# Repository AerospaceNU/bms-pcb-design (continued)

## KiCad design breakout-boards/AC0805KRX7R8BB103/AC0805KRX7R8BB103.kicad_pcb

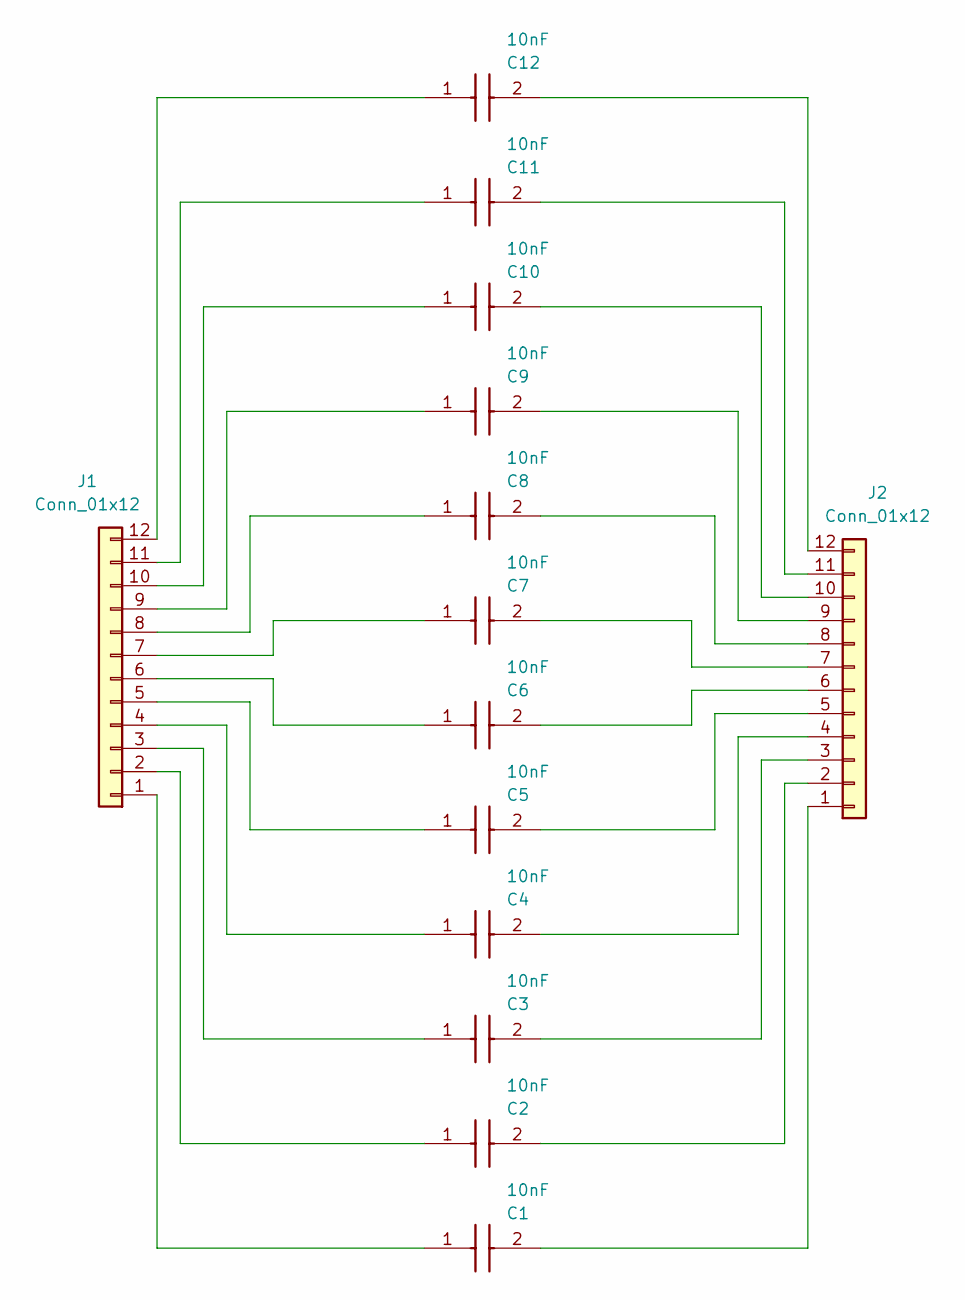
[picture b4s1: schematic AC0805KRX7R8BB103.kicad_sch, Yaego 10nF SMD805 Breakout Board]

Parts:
C1, C2, C3, C4, C5, C6, C7, C8, C9, C10, C11, C12: 10nF; CAPC2012X95N; Mouser Part Number 603-AC805KRX7R8BB103
J1, J2: Conn_01x12; PinSocket_1x12_P2.54mm_Vertical

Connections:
unnamed: C1.1, J1.1
unnamed: C2.1, J1.2
unnamed: C3.1, J1.3
unnamed: C4.1, J1.4
unnamed: C5.1, J1.5
unnamed: C6.1, J1.6
unnamed: C7.1, J1.7
unnamed: C8.1, J1.8
unnamed: C9.1, J1.9
unnamed: C10.1, J1.10
unnamed: C11.1, J1.11
unnamed: C12.1, J1.12
unnamed: C1.2, J2.1
unnamed: C2.2, J2.2
unnamed: C3.2, J2.3
unnamed: C4.2, J2.4
unnamed: C5.2, J2.5
unnamed: C6.2, J2.6
unnamed: C7.2, J2.7
unnamed: C8.2, J2.8
unnamed: C9.2, J2.9
unnamed: C10.2, J2.10
unnamed: C11.2, J2.11
unnamed: C12.2, J2.12

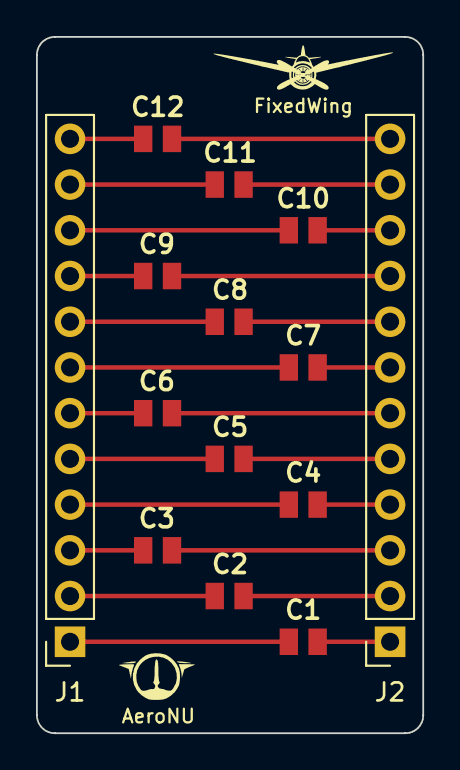
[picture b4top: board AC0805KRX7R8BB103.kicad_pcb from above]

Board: 2 copper layers, 21.5 x 38.7 mm, 16 parts (0 on the bottom side), 24 nets.

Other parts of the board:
AeroNU: LOGO; AeroNU - Logo (Smol)
FixedWing: LOGO; FixedWing - Logo (Smol)

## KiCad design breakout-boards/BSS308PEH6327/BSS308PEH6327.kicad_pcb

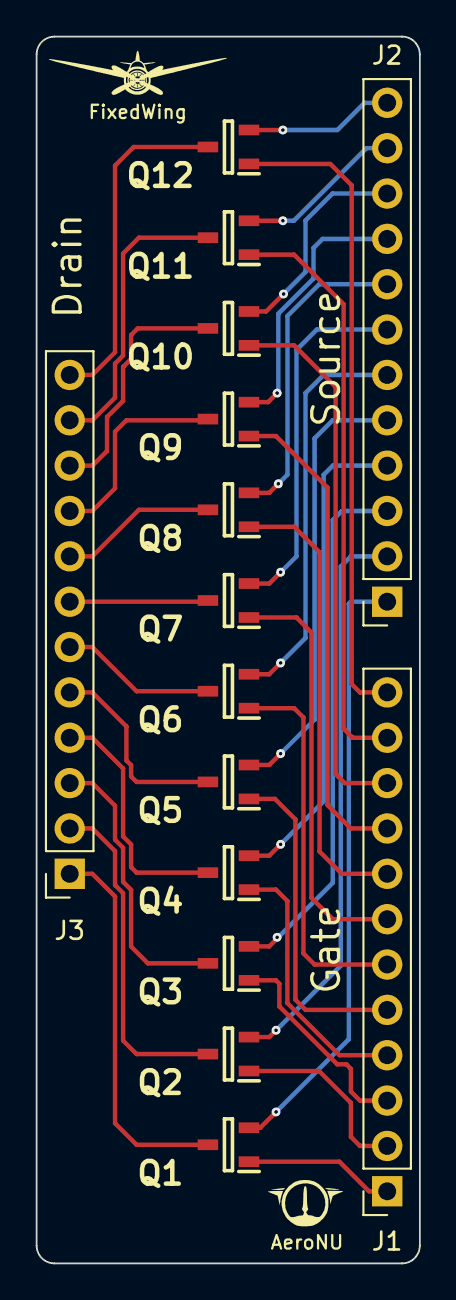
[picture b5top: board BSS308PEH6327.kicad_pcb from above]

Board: 2 copper layers, 21.5 x 68.7 mm, 17 parts (0 on the bottom side), 4 nets.

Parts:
AeroNU: LOGO; AeroNU - Logo (Smol)
FixedWing: LOGO; FixedWing - Logo (Smol)
J1, J2, J3: Conn_01x12; PinSocket_1x12_P2.54mm_Vertical
Q1, Q2, Q3, Q4, Q5, Q6, Q7, Q8, Q9, Q10, Q11, Q12: BSS308PE_H6327; SOT95P260X110-3N

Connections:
unnamed: J2.10, Q10.2 (S)
unnamed: J2.9, Q9.2 (S)
unnamed: J2.8, Q8.2 (S)
unnamed: J2.1, Q1.2 (S)

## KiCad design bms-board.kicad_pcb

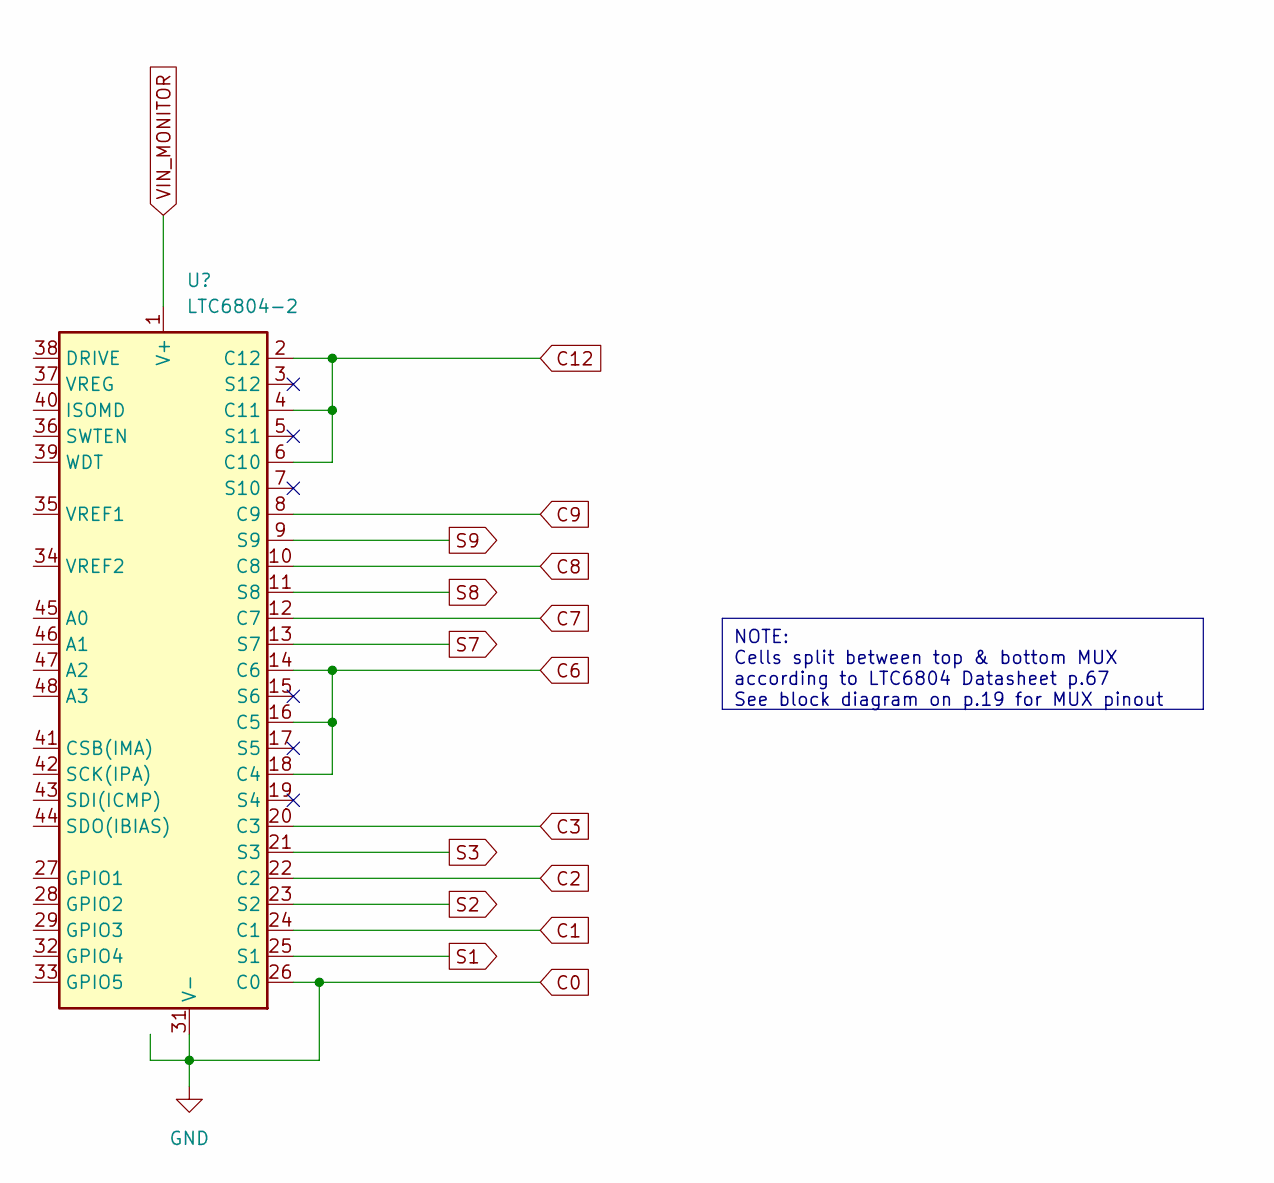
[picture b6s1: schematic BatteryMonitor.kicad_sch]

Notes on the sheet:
NOTE: Cells split between top & bottom MUX according to LTC6804 Datasheet p.67 See block diagram on p.19 for MUX pinout

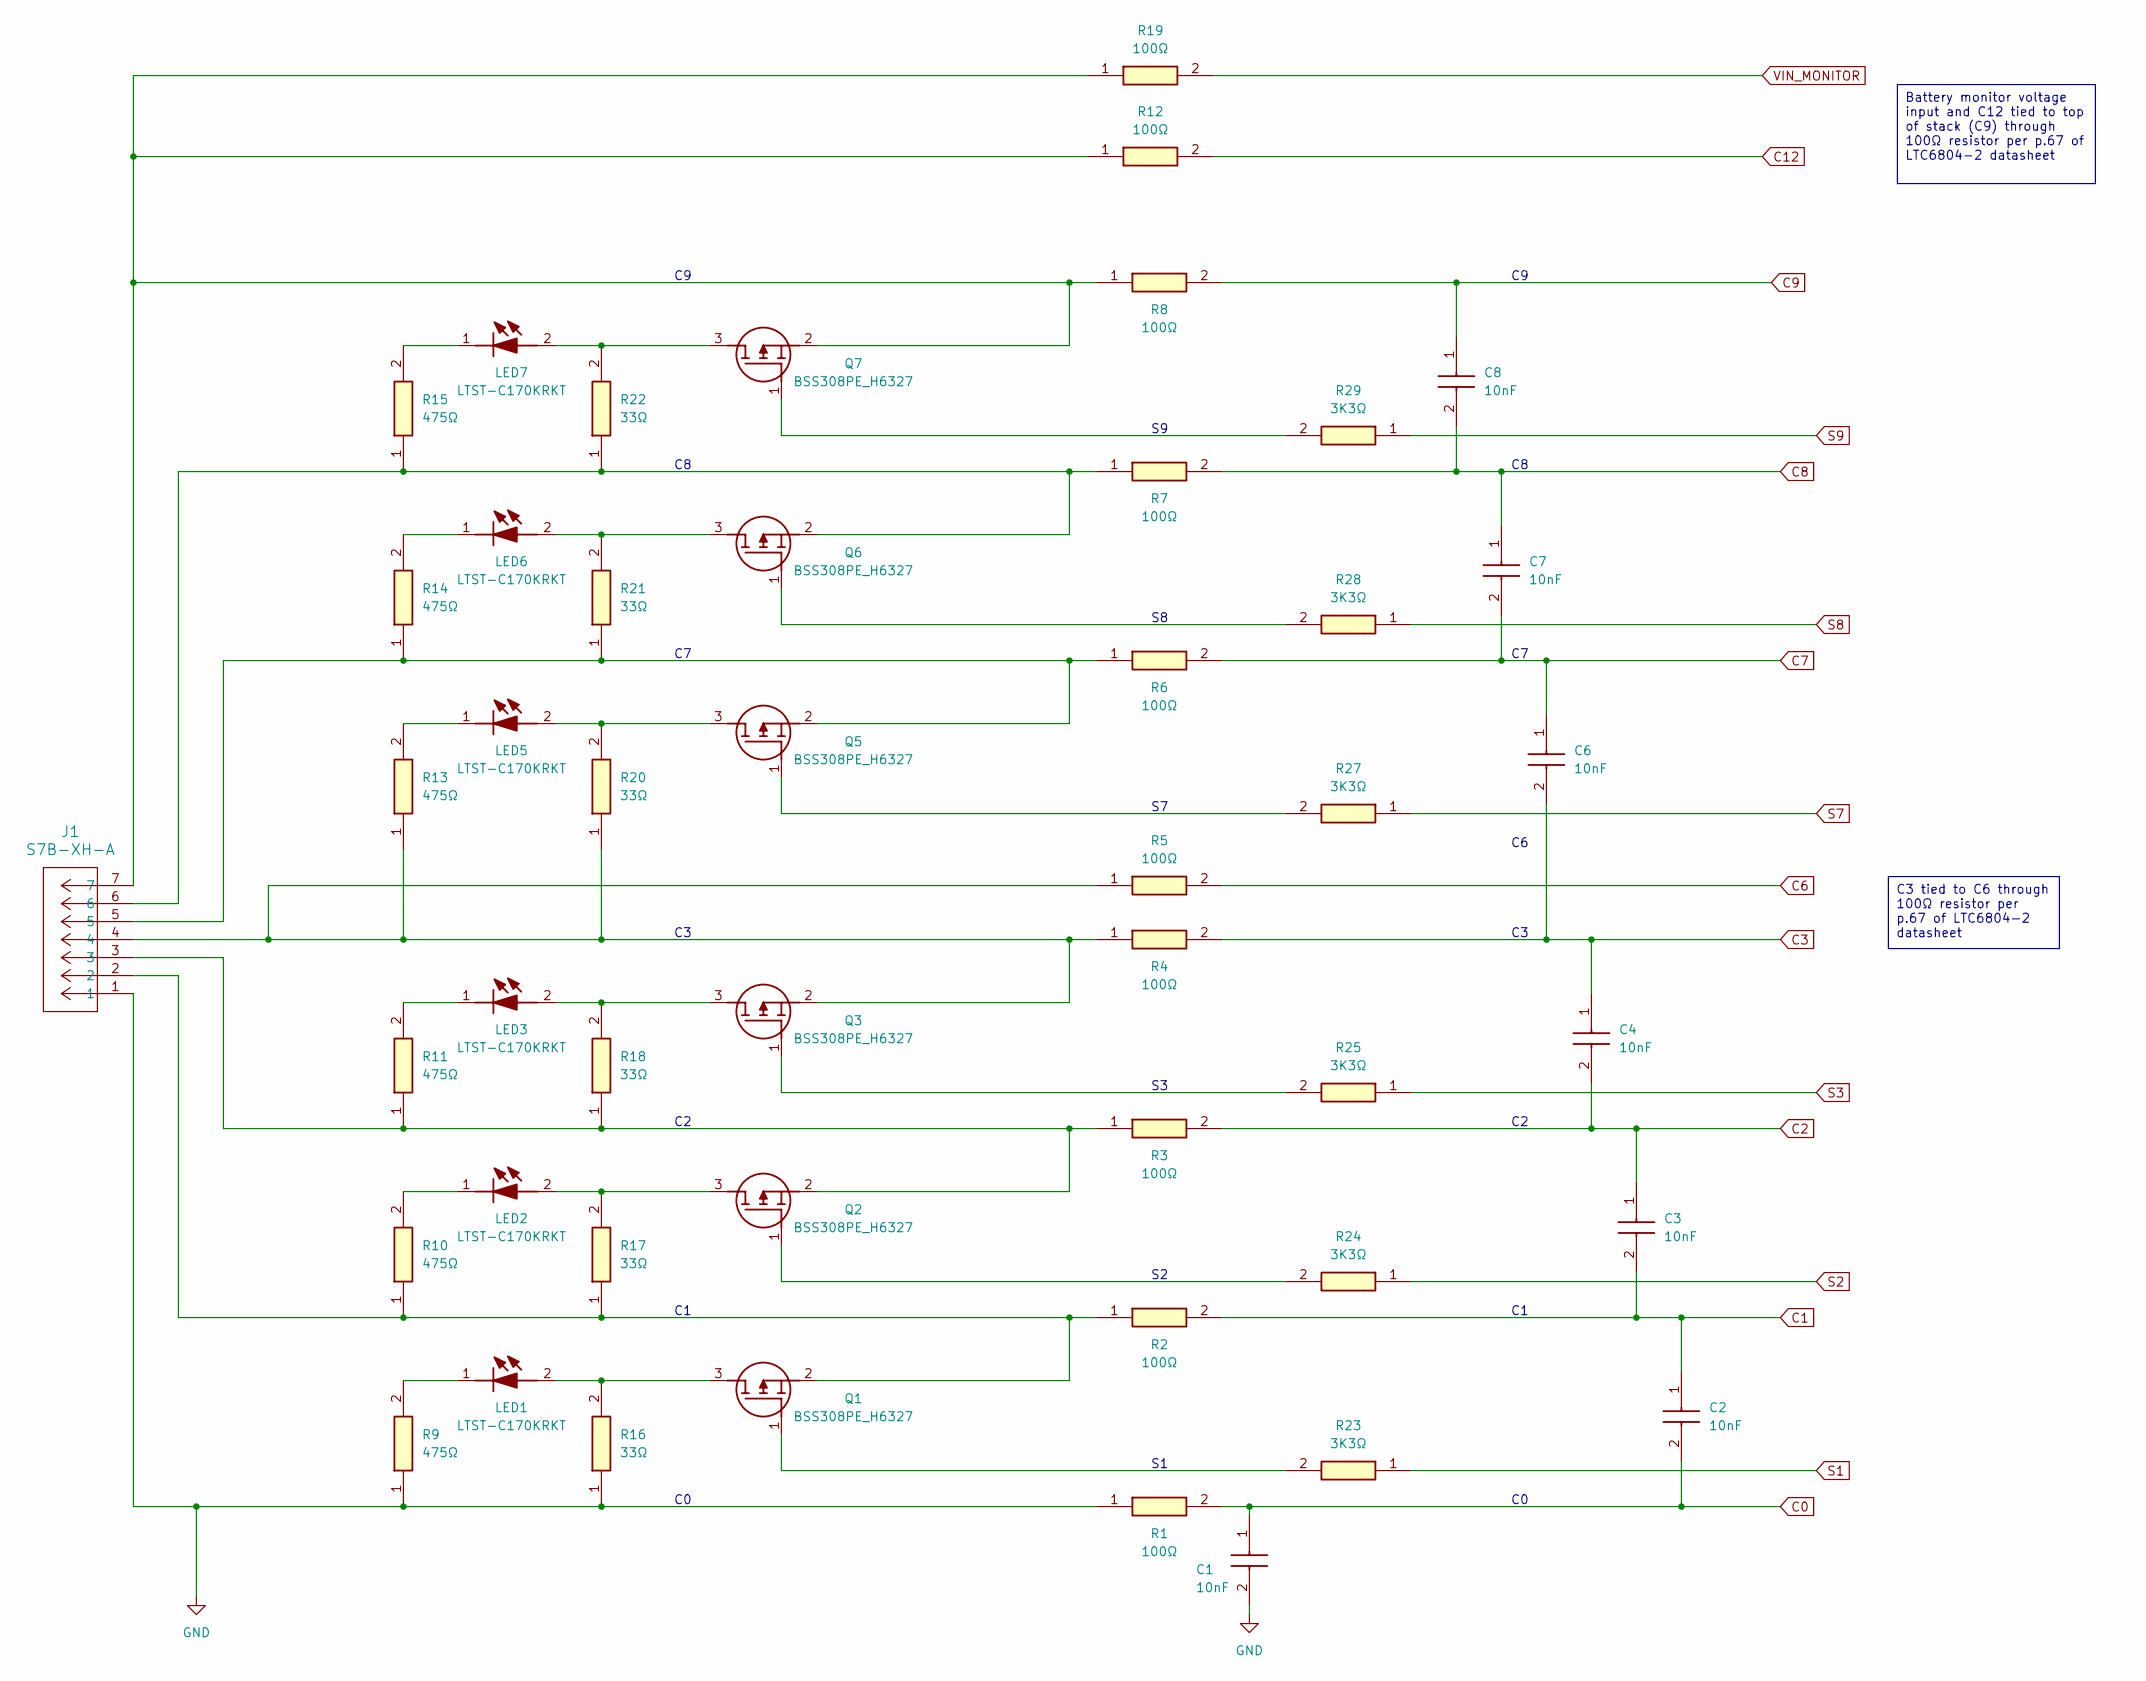
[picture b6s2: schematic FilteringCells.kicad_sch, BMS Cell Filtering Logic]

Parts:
C1, C2, C3, C4, C6, C7, C8: 10nF; CAPC2012X95N; Mouser Part Number 603-AC805KRX7R8BB103
J1: S7B-XH-A; CONN_S7B-XH-A_JST
LED1, LED2, LED3, LED5, LED6, LED7: LTST-C170KRKT; LEDC2012X120N; Mouser Part Number 859-LTST-C170KRKT
Q1, Q2, Q3, Q5, Q6, Q7: BSS308PE_H6327; SOT95P260X110-3N; Mouser Part Number 726-BSS308PEH6327
R1, R2, R3, R4, R5, R6, R7, R8, R12, R19: 100Ω; RESC2012X50N; Mouser Part Number 71-CRCW0805-100-E3
R9, R10, R11, R13, R14, R15: 475Ω; RESC2012X50N; Mouser Part Number 71-CRCW0805-475-E3
R16, R17, R18, R20, R21, R22: 33Ω; RESC6332X70N; Manufacturer_Part_Number CRCW251233R0FKEG
R23, R24, R25, R27, R28, R29: 3K3Ω; RESC2012X50N; Mouser Part Number 71-CRCW08053K30JNEA

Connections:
C0: C1.1, C1.2, C2.2, J1.1, R1.1, R1.2, R9.1, R16.1; also elsewhere on the board
C1: C2.1, C3.2, R2.2; also elsewhere on the board
C2: C3.1, C4.2, R3.2; also elsewhere on the board
C3: C4.1, C6.2, R4.2; also elsewhere on the board
C6: R5.2; also elsewhere on the board
C7: C6.1, C7.2, R6.2; also elsewhere on the board
C8: C7.1, C8.2, R7.2; also elsewhere on the board
C9: C8.1, R8.2; also elsewhere on the board
C12: R12.2; also elsewhere on the board
unnamed: LED1.2 (A), Q1.3 (D), R16.2
unnamed: LED1.1 (K), R9.2
unnamed: LED2.2 (A), Q2.3 (D), R17.2
unnamed: LED2.1 (K), R10.2
unnamed: LED3.2 (A), Q3.3 (D), R18.2
unnamed: LED3.1 (K), R11.2
unnamed: LED5.2 (A), Q5.3 (D), R20.2
unnamed: LED5.1 (K), R13.2
unnamed: LED6.2 (A), Q6.3 (D), R21.2
unnamed: LED6.1 (K), R14.2
unnamed: LED7.2 (A), Q7.3 (D), R22.2
unnamed: LED7.1 (K), R15.2
unnamed: Q1.1 (G), R23.2
unnamed: J1.2, Q1.2 (S), R2.1, R10.1, R17.1
unnamed: Q2.1 (G), R24.2
unnamed: J1.3, Q2.2 (S), R3.1, R11.1, R18.1
unnamed: Q3.1 (G), R25.2
unnamed: J1.4, Q3.2 (S), R4.1, R5.1, R13.1, R20.1
unnamed: Q5.1 (G), R27.2
unnamed: J1.5, Q5.2 (S), R6.1, R14.1, R21.1
unnamed: Q6.1 (G), R28.2
unnamed: J1.6, Q6.2 (S), R7.1, R15.1, R22.1
unnamed: Q7.1 (G), R29.2
unnamed: J1.7, Q7.2 (S), R8.1, R12.1, R19.1
S1: R23.1; also elsewhere on the board
S2: R24.1; also elsewhere on the board
S3: R25.1; also elsewhere on the board
S7: R27.1; also elsewhere on the board
S8: R28.1; also elsewhere on the board
S9: R29.1; also elsewhere on the board
VIN_MONITOR: R19.2; also elsewhere on the board

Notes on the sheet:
C3 tied to C6 through 100Ω resistor per p.67 of LTC6804-2 datasheet
Battery monitor voltage input and C12 tied to top of stack (C9) through 100Ω resistor per p.67 of LTC6804-2 datasheet

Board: 2 copper layers, 49 parts (0 on the bottom side), 40 nets, no tracks yet.

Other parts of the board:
U1: LTC6804-2; SSOP-48_5.3x12.8mm_P0.5mm

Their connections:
C0: U1.26 (C0), U1.30 (V-), U1.31 (V-); also elsewhere on the board
C1: U1.24 (C1); also elsewhere on the board
C2: U1.22 (C2); also elsewhere on the board
C3: U1.20 (C3); also elsewhere on the board
C6: U1.14 (C6), U1.16 (C5), U1.18 (C4); also elsewhere on the board
C7: U1.12 (C7); also elsewhere on the board
C8: U1.10 (C8); also elsewhere on the board
C9: U1.8 (C9); also elsewhere on the board
C12: U1.2 (C12), U1.4 (C11), U1.6 (C10); also elsewhere on the board
S1: U1.25 (S1); also elsewhere on the board
S2: U1.23 (S2); also elsewhere on the board
S3: U1.21 (S3); also elsewhere on the board
S7: U1.13 (S7); also elsewhere on the board
S8: U1.11 (S8); also elsewhere on the board
S9: U1.9 (S9); also elsewhere on the board
VIN_MONITOR: U1.1 (V+); also elsewhere on the board

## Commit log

2024-02-13 feat: initial commit
2024-02-15 feat: add 6804-2 kicad symbol
2024-02-15 feat: add 6804-2 kicad symbol (#3)
2024-02-16 TEMPLATE: add pull request description template
2024-02-16 feat: add automated git flow setup script
2024-02-16 update feature/add-cells branch to latest develop edition (#4)
    * feat: add 6804-2 kicad symbol
    * TEMPLATE: add pull request description template
    * feat: add automated git flow setup script
2024-02-16 update feature/our-symbol-library branch to latest develop edition (#5)
    * TEMPLATE: add pull request description template
    * feat: add automated git flow setup script
2024-02-20 feat: a maybe working fixed wing schematic symbol library
2024-02-21 feat: add line to checkout dev branch when running setup script
2024-02-21 feat: fix FixedWing symbol library to include LTC6804-2
2024-02-21 refactor: verifying symbol library works, remove individual ltc6804-2 symbol
2024-02-21 feat: adding needed files
2024-02-21 feat: edit conflict in setup script
2024-02-21 Merging new develop into new feature (#6)
    * feat: add 6804-2 kicad symbol
    * TEMPLATE: add pull request description template
    * feat: add automated git flow setup script
    * update feature/our-symbol-library branch to latest develop edition (#5)
    * TEMPLATE: add pull request description template
    * feat: add automated git flow setup script
2024-02-22 fix: changed symbol for easier schematic design and orginization by pin logic
2024-02-23 docs: Update pull_request_template.md
2024-02-23 Release/0.1 (#8)
    * feat: add 6804-2 kicad symbol
    * feat: add 6804-2 kicad symbol (#3)
    * TEMPLATE: add pull request description template
    * feat: add automated git flow setup script
    * update feature/add-cells branch to latest develop edition (#4)
    * feat: add 6804-2 kicad symbol
2024-03-07 feat: started adding cell nets
2024-03-19 feat: still some more LTC6804-2 symbol edits
2024-03-21 feat: add schematic hierarchy
2024-03-21 feat: add JST-XH 7pin symbol
2024-03-28 feat: add filtering components in library
2024-03-28 feat: add more symbols, some traces, sheet template
2024-03-30 feat: add filtering circuit
2024-03-30 feat: resolved splitting cells across monitor
2024-04-02 feat: add footprints
2024-04-02 feat: update PCB schematic
2024-04-02 feat: restructure project, move libraries to parent folder
2024-04-02 feat: restructure project, move libraries to parent folder (#13)
2024-04-03 refactor: move sheet template to libraries folder
2024-04-04 fix: add relative path to AeroNU sheet template
2024-04-04 refactor: previous commit but with changes this time :)
2024-04-04 feat: add breakout board templates for filtering circuit resistors
2024-04-04 feat: add breakout boards projects for remaining components
2024-04-05 refactor: remove subdirectory backups
2024-04-05 refactor: remove backups
2024-04-05 feat: create schematic for 10nf breakout board
2024-04-05 feat: add TestPoint footprint library
2024-04-20 feat: update bms references
2024-04-20 feat: Update FixedWing lib
2024-04-20 feat: add capacitor breakout board
2024-04-20 feat: add 100ohm resistor breakout board
2024-04-20 feat: add 3.3k ohm resistor breakout board
2024-04-20 feat: add 475ohm resistor breakout board
2024-04-20 feat: add 33ohm resistor breakout board
2024-04-20 feat: add red LED breakout board
2024-04-21 feat: create footprint for capacitor breakout board
2024-04-21 feat: create footprints for resistor breakout boards
2024-04-21 feat: create footprint for LED breakout board
2024-04-21 feat: add AeroNU and FixedWing silk screen logos
2024-04-23 feat: update MOSFET pcb and schem
2024-04-23 feat: add MOSFET PCB panel
2024-04-24 feat: change fixed wing logo and component positioning
2024-04-24 feat: create capacitor board panel
2024-04-24 fix: change board alignement
2024-04-24 feat: add panel and gerber files for 3.3k ohm breakout board
2024-04-25 feat: finalize 100ohm board design
2024-04-25 feat: finalize 3.3k ohm board design
2024-04-25 feat: finalize 470ohm board design
2024-04-25 feat: finalize 33ohm board design
2024-04-25 feat: finalize LED board design
2024-05-01 feat: add fillets to all boards
2024-06-28 Feature: add cells, create breakout boards, restructure project files (#14)
    * feat: started adding cell nets
    * feat: still some more LTC6804-2 symbol edits
    * feat: add schematic hierarchy
    * feat: add JST-XH 7pin symbol
    * feat: add filtering components in library
    * feat: add more symbols, some traces, sheet template
2024-07-13 hierarchical label conversion and readability changes
2024-07-14 feat: added minimal MCU schematic, 3D component model folder
2024-07-16 feat:continuing work on integrating RP2040 MCU
2024-07-16 feat: Added 3D models for connector and Flash ROM
2024-07-16 Added 3D Models in Cell Filtering and Balancing Sch.
2024-07-16 feat. Added most 3D models for footprints
2024-07-20 feat: continuing work on MCU circuit
2024-07-21 feat: finished preliminary RP2040 schematic design
2024-07-27 Feature: Add RP2040 MCU, folder for 3D models of components, continuing edits on other schematics (#15)
    * hierarchical label conversion and readability changes
    * feat: added minimal MCU schematic, 3D component model folder
    * feat:continuing work on integrating RP2040 MCU
    * feat: Added 3D models for connector and Flash ROM
    * Added 3D Models in Cell Filtering and Balancing Sch.
    * feat. Added most 3D models for footprints
2024-08-09 feat: initial 5V-reg-and-edits branch commit
2024-08-10 feat: small to-do list edits
2024-08-11 feat: put filtering and balancing circuits into hierarchical format
2024-08-11 feat: forgot to commit smol change
2024-08-12 feat: Added SiC461 Schematic, Footprint, and 3D Model
2024-08-13 feat: Added all components listed in the spreadsheet, until Inductor L1
2024-08-14 feat: forgor the description
2024-08-14 feat: Added all symbols and 3D models. Also began working on Regulator Schematic.
2024-08-14 feat: Added more connections to the 5V Regulator schematic.
2024-08-16 feat: Added VFB connection in 5V Regulator Schematic
2024-09-11 feat: Added 220uf cap & modified 5V Reg Circuit
2024-09-11 feat: Added more to 5V Regulator Schematic
2024-09-11 feat: Changed all resistor symbols to be the standard KiCAD symbol, started improving schematic.
2024-09-11 feat: Forgot to save changes to schematic.
2024-09-11 feat: Just about completed 5V Regulator Schematic.
2024-09-12 feat: cosmetic changes to 5V reg schematic
2024-09-12 feat: Added comment boxes and fixed 5V Regulator Schematic.
2024-09-13 feat: just moved around and edited notes on the 5V reg schematic
2024-09-17 feat: re-ordered page numbers
2024-09-19 feat: Added snubber circuit to 5V Regulator schematic
2024-09-20 feat: Added 0OHM jumper between ULTRASONIC and VDD, added LED indicator for PGOOD
2024-09-20 feat: added buncha shit, refer to tasks 4 and 8
2024-09-20 feat: finished 5V reg circuit lgtm!
2024-09-22 Feature: Added schematic and symbols for 5V switching regulator (#16)
    * feat: initial 5V-reg-and-edits branch commit
    * feat: small to-do list edits
    * feat: put filtering and balancing circuits into hierarchical format
    * feat: forgot to commit smol change
    * feat: Added SiC461 Schematic, Footprint, and 3D Model
    * feat: Added all components listed in the spreadsheet, until Inductor L1
2024-10-12 feat: making sure my git still works
2024-10-13 feat: figured out battery stack monitor V+ biasing. Refer to task 5 on the punchlist for more details.
2024-10-13 feat: swapped out battery<->18V diode for cheaper alternative
2024-11-02 feat: started a new sheet for external connections and added current sensor
2024-11-02 feat: made a placeholder label to connect current sensor to LTC6811 GPIO
2024-11-06 feat: added remaining connectors to component library
2024-11-06 Wired up most external connections
2024-11-06 feat: Just shifting a few things around
2024-11-07 Feature/current sensor (#17)
    * feat: making sure my git still works
    * feat: figured out battery stack monitor V+ biasing. Refer to task 5 on the punchlist for more details.
    * feat: swapped out battery<->18V diode for cheaper alternative
    * feat: started a new sheet for external connections and added current sensor
    * feat: made a placeholder label to connect current sensor to LTC6811 GPIO
    * feat: added remaining connectors to component library
2024-11-07 feat: first library migration commit
2024-12-29 feat: added sims directory, new cell balancing components
2024-12-31 feat: cell filtering/balancing switchover done
2025-01-03 feat: don't even know what I changed, just zoned out for several hours. Made PCB r/a mount XT-60s and solder pads into a 2-for-1 deal
2025-01-19 feat: schematic pretty much done
2025-01-29 feat: started layout
2025-02-13 feat: added current sense DAC
2025-02-14 feat: added capacitors to DAC
2025-02-14 feat:added more capacitors to DAC
2025-02-19 feat: more DAC capacitors
2025-02-19 feat: added temp sensor symbol/footprint
2025-02-19 added temp sense cad models
2025-02-21 feat: Added temp sensors
2025-02-25 feat: schematic cleanup, continued layout
2025-02-26 feat: added tvs protection ic to usb
2025-03-02 feat: placing cell filtering/balancing components
2025-03-11 feat: cell balancing board
2025-03-12 feat: lotta layout
2025-03-13 feat: changed cell balancing schem
2025-03-18 feat: slightly edited cell balance schem
2025-03-27 feat: big pre-design review schematic commit
2025-03-28 feat: post-design review clarity
2025-04-23 feat: I am so tired. 4-layer layout almost done
2025-06-12 feat: biiig layout and slight design change commit
2025-06-26 feat:bos->lax layout sesh
2025-06-26 feat: lax -> syd layout sesh
2025-07-02 feat: DRC run
2025-07-02 feat: deleted manufacturing files
2025-07-04 feat: silkscreen done
2025-07-15 feat: REV A COMMIT FOR FAB
2025-08-23 doc: updated schematic docs
2025-08-23 Feature/library migration (#19)
    * feat: first library migration commit
    * feat: added sims directory, new cell balancing components
    * feat: cell filtering/balancing switchover done
    * feat: don't even know what I changed, just zoned out for several hours. Made PCB r/a mount XT-60s and solder pads into a 2-for-1 deal
    * feat: schematic pretty much done
    * feat: started layout
2025-08-27 Rev A Release (#20)
    * Feature: add cells, create breakout boards, restructure project files (#14)
    * feat: started adding cell nets
    * feat: still some more LTC6804-2 symbol edits
    * feat: add schematic hierarchy
    * feat: add JST-XH 7pin symbol
    * feat: add filtering components in library
2025-09-09 hot fix: fix AP2114H-3.3TRG1 name
2026-04-23 hotfix: final rev. A cleanup
2026-04-23 hotfix: final cleanup of layout file formatting
2026-04-23 feat: generated pdfs
2026-05-06 feat: initial pass at rev. B
2026-05-06 feat: running DRC
2026-05-07 feat: DRC passed
2026-05-07 feat: finalizing BOM
2026-05-07 feat: Rev. B release
